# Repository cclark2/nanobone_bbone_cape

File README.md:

NanoBone BeagleBone Cape
========================

A cape connecting all BeagleBone P8/P9 I/Os to the pins of the $89 DE0-Nano FPGA board. Use it to add an FPGA to your BeagleBone project!

Special thanks to <a href="http://www.sparkfun.com/">SparkFun</a> for use of their open-source EAGLE libraries.

## Project Links
- <a href="http://www.hitchhikeree.org/beaglebone_capes/nanobone/">HitchhikerEE page</a>
- <a href="http://www.youtube.com/watch?v=jys_sxTUOd8">YouTube video</a>
- <a href="https://docs.google.com/folder/d/0B5HjtPsFD8u5YW9CNGdPOElQOEU/edit">Design files on Google Drive</a>
- <a href="http://beagleboard.org/CapeContest/entries/NanoBone/">BeagleBone Cape Contest page</a>

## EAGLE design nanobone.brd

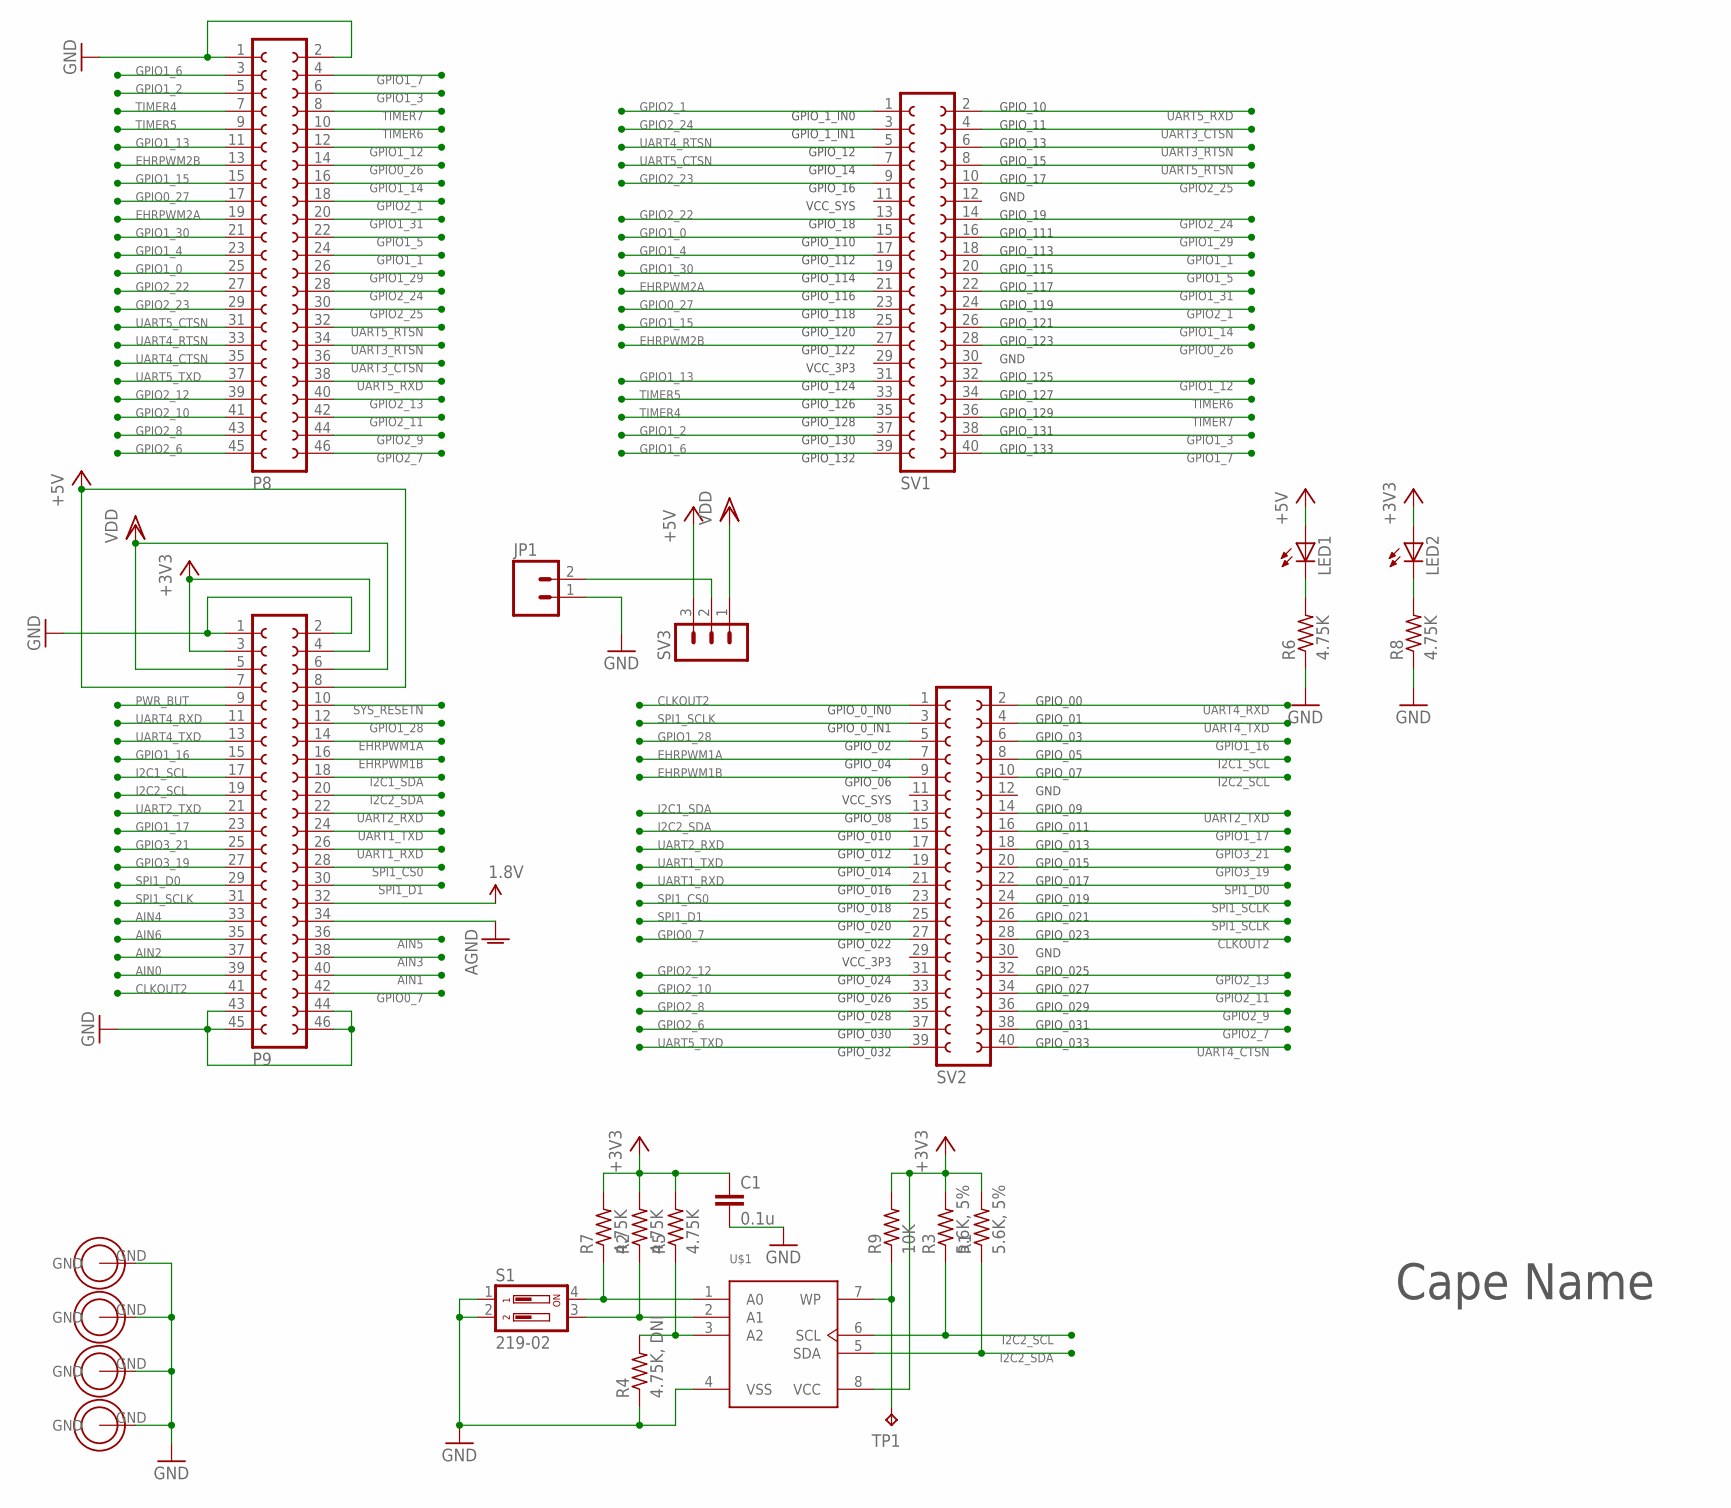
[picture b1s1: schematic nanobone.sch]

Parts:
C1: 0.1u; C0603
H1, H2, H3, H4: HOLE
JP1: M02LOCK_LONGPADS; 1X02_LOCK_LONGPADS
LED1, LED2: LEDCHIPLED_0603; CHIPLED_0603
P8, P9: FE23-2_SMD
R1, R3: 5.6K, 5%; R0603
R2, R5, R6, R7, R8: 4.75K; R0603
R4: 4.75K, DNI; R0603
R9: 10K; R0603
S1: 219-02; CTS-219-02
SV1, SV2: FE20-2
SV3: MA03-1
TP1: TPB2,54; B2,54
U$1: CAT24C256; SOIC8

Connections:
1.8V: P9.32
+3V3: C1.1, LED2.A, P9.3, P9.4, R1.2, R2.2, R3.2, R5.2, R7.2, R9.2, U$1.8 (VCC)
+5V: LED1.A, P9.7, P9.8, SV3.3
AGND: P9.34
AIN0: P9.39
AIN1: P9.40
AIN2: P9.37
AIN3: P9.38
AIN4: P9.33
AIN5: P9.36
AIN6: P9.35
CLKOUT2: P9.41, SV2.1, SV2.28
EHRPWM1A: P9.14, SV2.7
EHRPWM1B: P9.16, SV2.9
EHRPWM2A: P8.19, SV1.21
EHRPWM2B: P8.13, SV1.27
GND: C1.2, H1.GND, H2.GND, H3.GND, H4.GND, JP1.1, P8.1, P8.2, P9.1, P9.2, P9.43, P9.44, P9.45, P9.46, R4.1, R6.1, R8.1, S1.1, S1.2, U$1.4 (VSS)
GPIO0_7: P9.42, SV2.27
GPIO0_26: P8.14, SV1.28
GPIO0_27: P8.17, SV1.23
GPIO1_0: P8.25, SV1.15
GPIO1_1: P8.24, SV1.18
GPIO1_2: P8.5, SV1.37
GPIO1_3: P8.6, SV1.38
GPIO1_4: P8.23, SV1.17
GPIO1_5: P8.22, SV1.20
GPIO1_6: P8.3, SV1.39
GPIO1_7: P8.4, SV1.40
GPIO1_12: P8.12, SV1.32
GPIO1_13: P8.11, SV1.31
GPIO1_14: P8.16, SV1.26
GPIO1_15: P8.15, SV1.25
GPIO1_16: P9.15, SV2.6
GPIO1_17: P9.23, SV2.16
GPIO1_28: P9.12, SV2.5
GPIO1_29: P8.26, SV1.16
GPIO1_30: P8.21, SV1.19
GPIO1_31: P8.20, SV1.22
GPIO2_1: P8.18, SV1.1, SV1.24
GPIO2_6: P8.45, SV2.37
GPIO2_7: P8.46, SV2.38
GPIO2_8: P8.43, SV2.35
GPIO2_9: P8.44, SV2.36
GPIO2_10: P8.41, SV2.33
GPIO2_11: P8.42, SV2.34
GPIO2_12: P8.39, SV2.31
GPIO2_13: P8.40, SV2.32
GPIO2_22: P8.27, SV1.13
GPIO2_23: P8.29, SV1.9
GPIO2_24: P8.28, SV1.3, SV1.14
GPIO2_25: P8.30, SV1.10
GPIO3_19: P9.27, SV2.20
GPIO3_21: P9.25, SV2.18
I2C1_SCL: P9.17, SV2.8
I2C1_SDA: P9.18, SV2.13
I2C2_SCL: P9.19, R3.1, SV2.10, U$1.6 (SCL)
I2C2_SDA: P9.20, R1.1, SV2.15, U$1.5 (SDA)
unnamed: R7.1, S1.4, U$1.1 (A0)
unnamed: R2.1, S1.3, U$1.2 (A1)
unnamed: R4.2, R5.1, U$1.3 (A2)
unnamed: JP1.2, SV3.2
unnamed: R9.1, TP1.TP, U$1.7 (WP)
unnamed: LED1.C, R6.2
unnamed: LED2.C, R8.2
PWR_BUT: P9.9
SPI1_CS0: P9.28, SV2.23
SPI1_D0: P9.29, SV2.22
SPI1_D1: P9.30, SV2.25
SPI1_SCLK: P9.31, SV2.3, SV2.24, SV2.26
SYS_RESETN: P9.10
TIMER4: P8.7, SV1.35
TIMER5: P8.9, SV1.33
TIMER6: P8.10, SV1.34
TIMER7: P8.8, SV1.36
UART1_RXD: P9.26, SV2.21
UART1_TXD: P9.24, SV2.19
UART2_RXD: P9.22, SV2.17
UART2_TXD: P9.21, SV2.14
UART3_CTSN: P8.36, SV1.4
UART3_RTSN: P8.34, SV1.6
UART4_CTSN: P8.35, SV2.40
UART4_RTSN: P8.33, SV1.5
UART4_RXD: P9.11, SV2.2
UART4_TXD: P9.13, SV2.4
UART5_CTSN: P8.31, SV1.7
UART5_RTSN: P8.32, SV1.8
UART5_RXD: P8.38, SV1.2
UART5_TXD: P8.37, SV2.39
VDD: P9.5, P9.6, SV3.1

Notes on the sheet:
Cape Name
GPIO_0_IN0
GPIO_00
GPIO_01
GPIO_03
GPIO_05
GPIO_07
GND
GPIO_09
GPIO_011
GPIO_013
GPIO_015
GPIO_017
GPIO_019
GPIO_021
GPIO_023
GPIO_025
GPIO_027
GPIO_029
GPIO_031
GPIO_033
GPIO_10
GPIO_11
GPIO_13
GPIO_15
GPIO_17
GPIO_19
GPIO_111
GPIO_113
GPIO_115
GPIO_117
GPIO_119
GPIO_121
GPIO_123
GPIO_125
GPIO_127
GPIO_129
GPIO_131
GPIO_133
GPIO_1_IN0

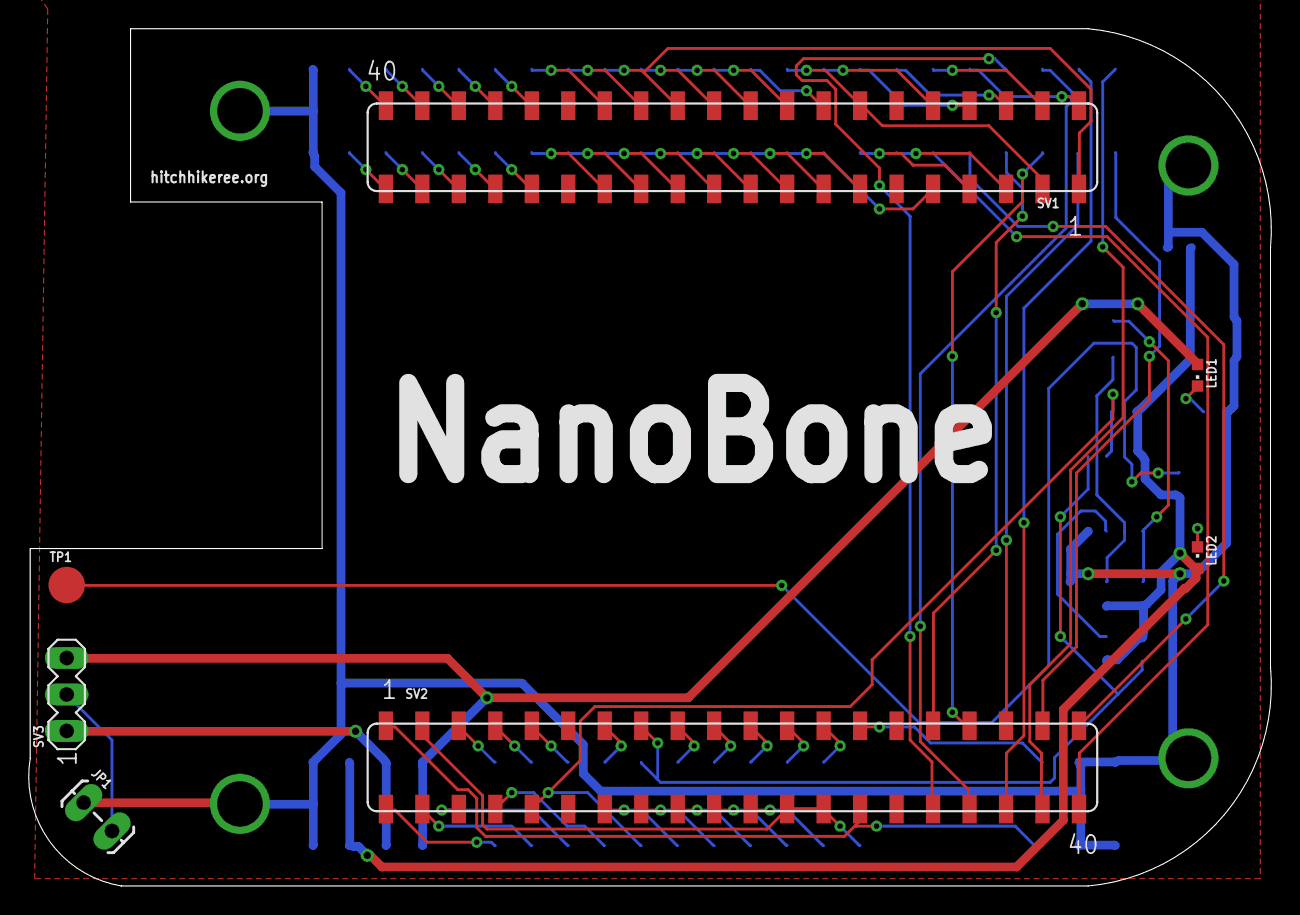
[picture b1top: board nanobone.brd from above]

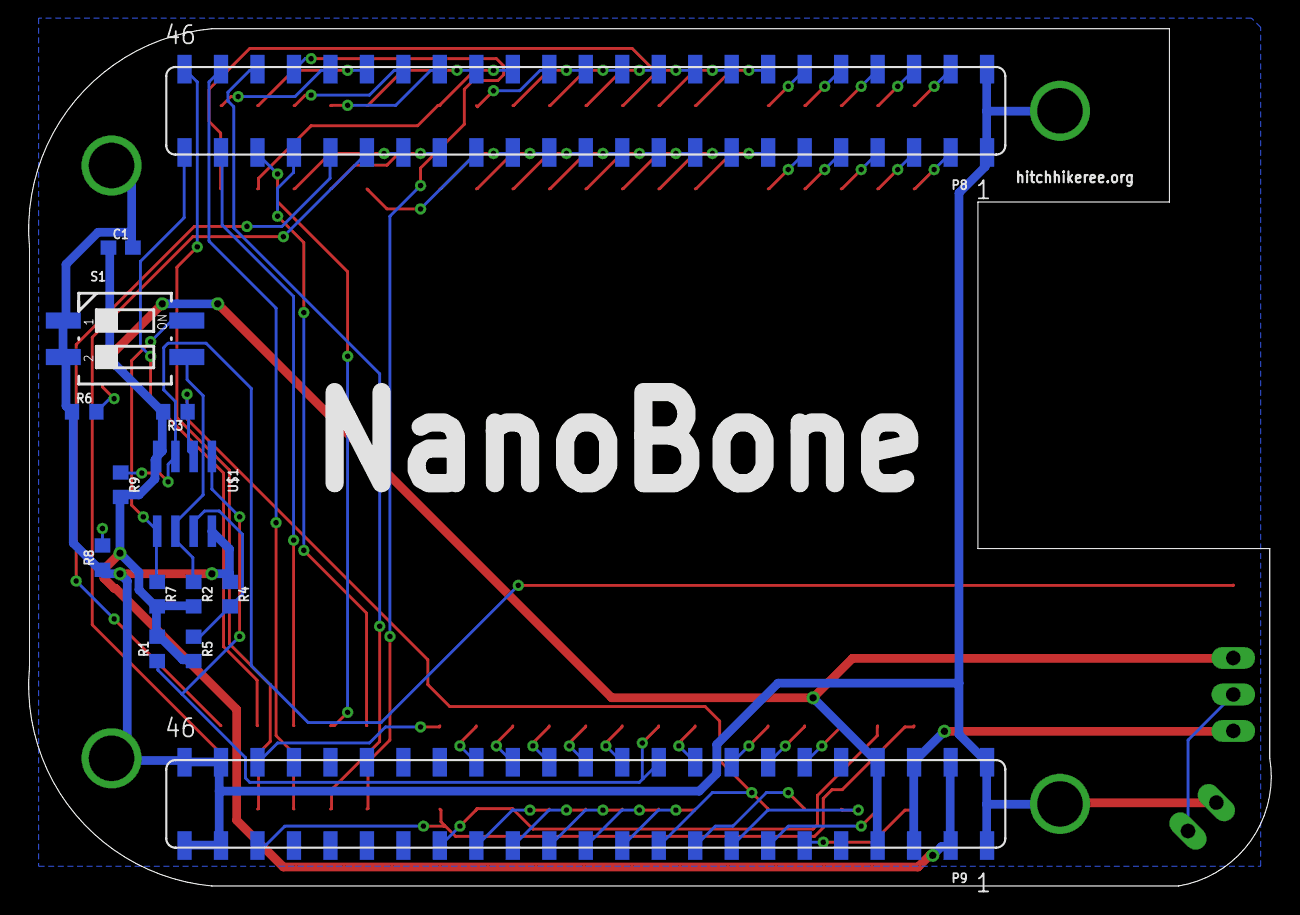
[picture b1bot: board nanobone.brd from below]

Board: 2 copper layers, 86.5 x 59.7 mm, 25 parts (14 on the bottom side), 78 nets.

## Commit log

2013-01-01 Design complete, cleanup needed.
2013-01-01 BOM done.
2013-01-06 Added BOM prices, added PDFs of design, sorted files.

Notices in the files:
parts and their libraries:
SparkFun-Connectors: Licensing: CC v3.0 Share-Alike You are welcome to use this library for commercial purposes.
